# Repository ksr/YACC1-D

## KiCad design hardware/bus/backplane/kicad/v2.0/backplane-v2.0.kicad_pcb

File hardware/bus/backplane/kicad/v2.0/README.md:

# backplane-v2.0 — KiCad conversion

Generated 2026-09-23 by `tools/eagle_to_kicad_all.py` from the Eagle design `yacc2buss` in `hardware/bus/backplane/eagle/v2.0/`. **The Eagle files are the record of what was designed and built; this KiCad project is derived from them and is regenerated from scratch on every run of the tool** (hand edits here will be lost - once a card is edited in KiCad, remove it from the tool's list). This revision was FABRICATED (see `hardware/FABRICATED.md`).

## Files

| File | What it is |
|---|---|
| `backplane-v2.0.kicad_pro` | project; OSH Park rules (6 mil track, 5 mil clearance, 10 mil drill, 4 mil annular) |
| `backplane-v2.0.kicad_sch` | root sheet; 1 sub-sheet(s) `backplane-v2.0-sheetN.kicad_sch` mirror the Eagle sheets |
| `backplane-v2.0-eagle.kicad_sym` | project symbol library generated from the Eagle libraries used (units = Eagle gates) |
| `backplane-v2.0.kicad_pcb` | the board: 4 copper layers, 29 footprints, 8523 track segments, 1388 vias |
| `backplane-v2.0-eagle.pretty/` | project footprint library extracted from the imported board |
| `reports/` | ERC (`erc.json`), DRC (`drc.json`), schematic PDF, board renders (`-top.png`, `-bottom.png`), netlist + `netlist-compare.txt` |

## Proof

Schematic-vs-board netlist comparison (`tools/kicad/compare_netlists.py`: every (reference, pad) partition must be identical): **MATCH (87/87 nets)**

```
  same connectivity, different net name: [('/Sheet 1/SIG0', 'SIG0'), ('/Sheet 1/SIG1', 'SIG1'), ('/Sheet 1/SIG2', 'SIG2'), ('/Sheet 1/SIG3', 'SIG3'), ('/Sheet 1/SIG4', 'SIG4'), ('/Sheet 1/SIG5', 'SIG5'), ('/Sheet 1/SIG6', 'SIG6'), ('/Sheet 1/SIG7', 'SIG7'), ('/Sheet 1/SIG8', 'SIG8'), ('/Sheet 1/SIG9', 'SIG9'), ('/Sheet 1/SIG10', 'SIG10'), ('/Sheet 1/SIG11', 'SIG11'), ('/Sheet 1/SIG12', 'SIG12'), ('/Sheet 1/SIG13', 'SIG13'), ('/Sheet 1/SIG14', 'SIG14'), ('/Sheet 1/SIG15', 'SIG15'), ('/Sheet 1/SIG16', 'SIG16'), ('/Sheet 1/SIG17', 'SIG17'), ('/Sheet 1/SIG18', 'SIG18'), ('/Sheet 1/SIG19', 'SIG19'), ('/Sheet 1/SIG20', 'SIG20'), ('/Sheet 1/SIG21', 'SIG21'), ('/Sheet 1/SIG22', 'SIG22'), ('/Sheet 1/SIG23', 'SIG23'), ('/Sheet 1/SIG24', 'SIG24'), ('/Sheet 1/SIG25', 'SIG25'), ('/Sheet 1/SIG26', 'SIG26'), ('/Sheet 1/SIG27', 'SIG27'), ('/Sheet 1/SIG28', 'SIG28'), ('/Sheet 1/SIG29', 'SIG29'), ('/Sheet 1/SIG30', 'SIG30'), ('/Sheet 1/SIG31', 'SIG31'), ('/Sheet 1/SIG32', 'SIG32'), ('/Sheet 1/SIG33', 'SIG33'), ('/Sheet 1/SIG34', 'SIG34'), ('/Sheet 1/SIG35', 'SIG35'), ('/Sheet 1/SIG36', 'SIG36'), ('/Sheet 1/SIG37', 'SIG37'), ('/Sheet 1/SIG38', 'SIG38'), ('/Sheet 1/SIG39', 'SIG39'), ('/Sheet 1/SIG40', 'SIG40'), ('/Sheet 1/SIG41', 'SIG41'), ('/Sheet 1/SIG42', 'SIG42'), ('/Sheet 1/SIG43', 'SIG43'), ('/Sheet 1/SIG44', 'SIG44'), ('/Sheet 1/SIG45', 'SIG45'), ('/Sheet 1/SIG46', 'SIG46'), ('/Sheet 1/SIG47', 'SIG47'), ('/Sheet 1/SIG48', 'SIG48'), ('/Sheet 1/SIG49', 'SIG49'), ('/Sheet 1/SIG50', 'SIG50'), ('/Sheet 1/SIG51', 'SIG51'), ('/Sheet 1/SIG52', 'SIG52'), ('/Sheet 1/SIG53', 'SIG53'), ('/Sheet 1/SIG54', 'SIG54'), ('/Sheet 1/SIG55', 'SIG55'), ('/Sheet 1/SIG56', 'SIG56'), ('/Sheet 1/SIG57', 'SIG57'), ('/Sheet 1/SIG58', 'SIG58'), ('/Sheet 1/SIG59', 'SIG59'), ('/Sheet 1/SIG60', 'SIG60'), ('/Sheet 1/SIG61', 'SIG61'), ('/Sheet 1/SIG62', 'SIG62'), ('/Sheet 1/SIG63', 'SIG63'), ('/Sheet 1/SIG64', 'SIG64'), ('/Sheet 1/SIG65', 'SIG65'), ('/Sheet 1/SIG66', 'SIG66'), ('/Sheet 1/SIG67', 'SIG67'), ('/Sheet 1/SIG68', 'SIG68'), ('/Sheet 1/SIG69', 'SIG69'), ('/Sheet 1/SIG70', 'SIG70'), ('/Sheet 1/SIG71', 'SIG71'), ('/Sheet 1/SIG72', 'SIG72'), ('/Sheet 1/SIG73', 'SIG73'), ('/Sheet 1/SIG74', 'SIG74'), ('/Sheet 1/SIG75', 'SIG75'), ('/Sheet 1/SIG76', 'SIG76'), ('/Sheet 1/SIG77', 'SIG77'), ('/Sheet 1/SIG78', 'SIG78'), ('/Sheet 1/SIG79', 'SIG79'), ('/Sheet 1/SIG80', 'SIG80'), ('/Sheet 1/SIG81', 'SIG81'), ('/Sheet 1/SIG82', 'SIG82'), ('/Sheet 1/SIG83', 'SIG83'), ('Net-(PWR0-PadA)', 'N$2')]
```

## Readability

`tools/kicad/sch_overlaps.py` over every sheet: text over text 7, text over a symbol body 559, text crossed by a line 9, items off the drawing frame or on the title block 0. What is left is mostly the Eagle drawing itself (parts placed that close in Eagle) or KiCad drawing pin numbers centred on short pins.

## Residual ERC / DRC

ERC by type: none.
`isolated_pin_label` = the converter's per-net global labels (cosmetic); `power_pin_not_driven` / unused-unit notes are the same ones KiCad's own Eagle importer leaves. `unconnected_wire_endpoint` / `pin_not_connected` = wire stubs Eagle leaves bare (mostly net wires ending on a bus, which is drawn as graphics here); since 2026-09-23 the converter no longer hangs a label on every such end (that was most of the label clutter), so they show as KiCad warnings.

DRC by type: clearance 3, items_not_allowed 16, lib_footprint_mismatch 8, shorting_items 16, silk_over_copper 4, silk_overlap 76; unconnected items 0; schematic parity 0.
Silk-over-pad and clearance notes reflect the Eagle design as drawn; unconnected items are Eagle airwires (parts the design left unrouted).

Converter: converted: 56 symbols, 891 wires, 672 labels, 135 junctions, 8 bus lines, 0 no-connects

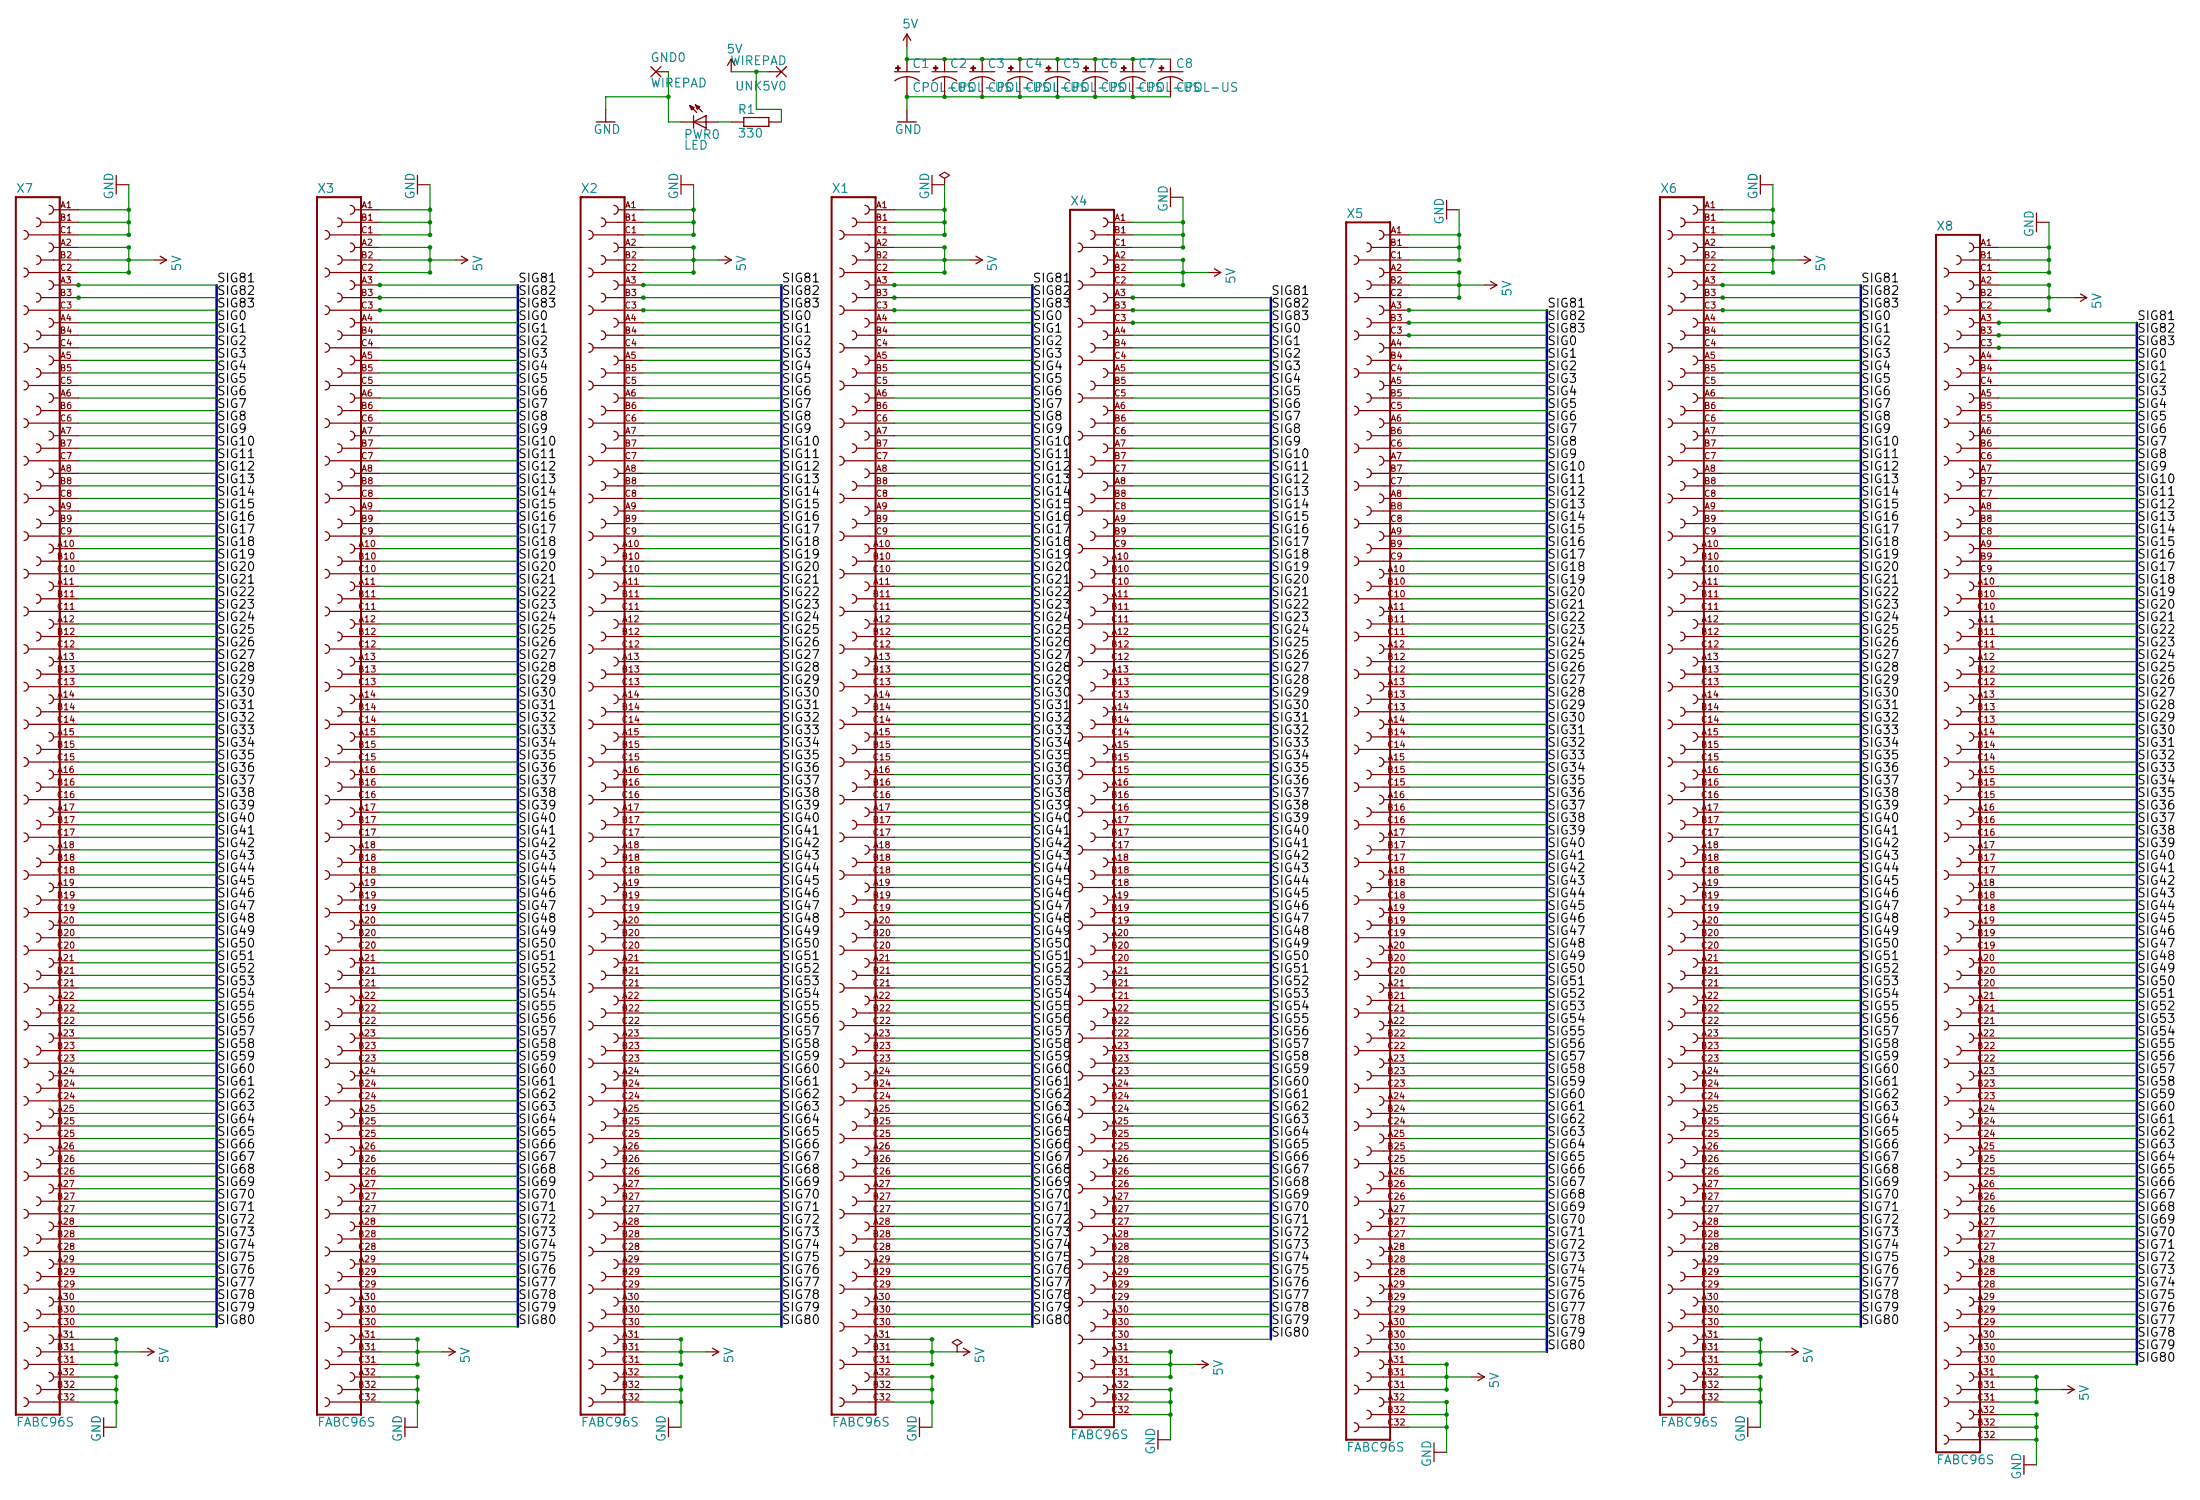
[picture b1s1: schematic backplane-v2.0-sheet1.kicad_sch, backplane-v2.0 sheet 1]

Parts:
C1, C2, C3, C4, C5, C6, C7, C8: CPOL-US; E5-6
GND0: WIREPAD; 4,16O1,6
PWR0: LED; LED5MM
R1: 330; 0207_10
UNK5V0: WIREPAD; 4,16O1,6
X1, X2, X3, X4, X5, X6, X7, X8: FABC96S

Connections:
5V: C1.+, C2.+, C3.+, C4.+, C5.+, C6.+, C7.+, C8.+, R1.2, UNK5V0.1, X1.A2, X1.A31, X1.B2, X1.B31, X1.C2, X1.C31, X2.A2, X2.A31, X2.B2, X2.B31, X2.C2, X2.C31, X3.A2, X3.A31, X3.B2, X3.B31, X3.C2, X3.C31, X4.A2, X4.A31, X4.B2, X4.B31, X4.C2, X4.C31, X5.A2, X5.A31, X5.B2, X5.B31, X5.C2, X5.C31, X6.A2, X6.A31, X6.B2, X6.B31, X6.C2, X6.C31, X7.A2, X7.A31, X7.B2, X7.B31, X7.C2, X7.C31, X8.A2, X8.A31, X8.B2, X8.B31, X8.C2, X8.C31
GND: C1.-, C2.-, C3.-, C4.-, C5.-, C6.-, C7.-, C8.-, GND0.1, PWR0.K (C), X1.A1, X1.A32, X1.B1, X1.B32, X1.C1, X1.C32, X2.A1, X2.A32, X2.B1, X2.B32, X2.C1, X2.C32, X3.A1, X3.A32, X3.B1, X3.B32, X3.C1, X3.C32, X4.A1, X4.A32, X4.B1, X4.B32, X4.C1, X4.C32, X5.A1, X5.A32, X5.B1, X5.B32, X5.C1, X5.C32, X6.A1, X6.A32, X6.B1, X6.B32, X6.C1, X6.C32, X7.A1, X7.A32, X7.B1, X7.B32, X7.C1, X7.C32, X8.A1, X8.A32, X8.B1, X8.B32, X8.C1, X8.C32
unnamed: PWR0.A, R1.1
SIG0: X1.A4, X2.A4, X3.A4, X4.A4, X5.A4, X6.A4, X7.A4, X8.A4
SIG1: X1.B4, X2.B4, X3.B4, X4.B4, X5.B4, X6.B4, X7.B4, X8.B4
SIG2: X1.C4, X2.C4, X3.C4, X4.C4, X5.C4, X6.C4, X7.C4, X8.C4
SIG3: X1.A5, X2.A5, X3.A5, X4.A5, X5.A5, X6.A5, X7.A5, X8.A5
SIG4: X1.B5, X2.B5, X3.B5, X4.B5, X5.B5, X6.B5, X7.B5, X8.B5
SIG5: X1.C5, X2.C5, X3.C5, X4.C5, X5.C5, X6.C5, X7.C5, X8.C5
SIG6: X1.A6, X2.A6, X3.A6, X4.A6, X5.A6, X6.A6, X7.A6, X8.A6
SIG7: X1.B6, X2.B6, X3.B6, X4.B6, X5.B6, X6.B6, X7.B6, X8.B6
SIG8: X1.C6, X2.C6, X3.C6, X4.C6, X5.C6, X6.C6, X7.C6, X8.C6
SIG9: X1.A7, X2.A7, X3.A7, X4.A7, X5.A7, X6.A7, X7.A7, X8.A7
SIG10: X1.B7, X2.B7, X3.B7, X4.B7, X5.B7, X6.B7, X7.B7, X8.B7
SIG11: X1.C7, X2.C7, X3.C7, X4.C7, X5.C7, X6.C7, X7.C7, X8.C7
SIG12: X1.A8, X2.A8, X3.A8, X4.A8, X5.A8, X6.A8, X7.A8, X8.A8
SIG13: X1.B8, X2.B8, X3.B8, X4.B8, X5.B8, X6.B8, X7.B8, X8.B8
SIG14: X1.C8, X2.C8, X3.C8, X4.C8, X5.C8, X6.C8, X7.C8, X8.C8
SIG15: X1.A9, X2.A9, X3.A9, X4.A9, X5.A9, X6.A9, X7.A9, X8.A9
SIG16: X1.B9, X2.B9, X3.B9, X4.B9, X5.B9, X6.B9, X7.B9, X8.B9
SIG17: X1.C9, X2.C9, X3.C9, X4.C9, X5.C9, X6.C9, X7.C9, X8.C9
SIG18: X1.A10, X2.A10, X3.A10, X4.A10, X5.A10, X6.A10, X7.A10, X8.A10
SIG19: X1.B10, X2.B10, X3.B10, X4.B10, X5.B10, X6.B10, X7.B10, X8.B10
SIG20: X1.C10, X2.C10, X3.C10, X4.C10, X5.C10, X6.C10, X7.C10, X8.C10
SIG21: X1.A11, X2.A11, X3.A11, X4.A11, X5.A11, X6.A11, X7.A11, X8.A11
SIG22: X1.B11, X2.B11, X3.B11, X4.B11, X5.B11, X6.B11, X7.B11, X8.B11
SIG23: X1.C11, X2.C11, X3.C11, X4.C11, X5.C11, X6.C11, X7.C11, X8.C11
SIG24: X1.A12, X2.A12, X3.A12, X4.A12, X5.A12, X6.A12, X7.A12, X8.A12
SIG25: X1.B12, X2.B12, X3.B12, X4.B12, X5.B12, X6.B12, X7.B12, X8.B12
SIG26: X1.C12, X2.C12, X3.C12, X4.C12, X5.C12, X6.C12, X7.C12, X8.C12
SIG27: X1.A13, X2.A13, X3.A13, X4.A13, X5.A13, X6.A13, X7.A13, X8.A13
SIG28: X1.B13, X2.B13, X3.B13, X4.B13, X5.B13, X6.B13, X7.B13, X8.B13
SIG29: X1.C13, X2.C13, X3.C13, X4.C13, X5.C13, X6.C13, X7.C13, X8.C13
SIG30: X1.A14, X2.A14, X3.A14, X4.A14, X5.A14, X6.A14, X7.A14, X8.A14
SIG31: X1.B14, X2.B14, X3.B14, X4.B14, X5.B14, X6.B14, X7.B14, X8.B14
SIG32: X1.C14, X2.C14, X3.C14, X4.C14, X5.C14, X6.C14, X7.C14, X8.C14
SIG33: X1.A15, X2.A15, X3.A15, X4.A15, X5.A15, X6.A15, X7.A15, X8.A15
SIG34: X1.B15, X2.B15, X3.B15, X4.B15, X5.B15, X6.B15, X7.B15, X8.B15
SIG35: X1.C15, X2.C15, X3.C15, X4.C15, X5.C15, X6.C15, X7.C15, X8.C15
SIG36: X1.A16, X2.A16, X3.A16, X4.A16, X5.A16, X6.A16, X7.A16, X8.A16
SIG37: X1.B16, X2.B16, X3.B16, X4.B16, X5.B16, X6.B16, X7.B16, X8.B16
SIG38: X1.C16, X2.C16, X3.C16, X4.C16, X5.C16, X6.C16, X7.C16, X8.C16
SIG39: X1.A17, X2.A17, X3.A17, X4.A17, X5.A17, X6.A17, X7.A17, X8.A17
SIG40: X1.B17, X2.B17, X3.B17, X4.B17, X5.B17, X6.B17, X7.B17, X8.B17
SIG41: X1.C17, X2.C17, X3.C17, X4.C17, X5.C17, X6.C17, X7.C17, X8.C17
SIG42: X1.A18, X2.A18, X3.A18, X4.A18, X5.A18, X6.A18, X7.A18, X8.A18
SIG43: X1.B18, X2.B18, X3.B18, X4.B18, X5.B18, X6.B18, X7.B18, X8.B18
SIG44: X1.C18, X2.C18, X3.C18, X4.C18, X5.C18, X6.C18, X7.C18, X8.C18
SIG45: X1.A19, X2.A19, X3.A19, X4.A19, X5.A19, X6.A19, X7.A19, X8.A19
SIG46: X1.B19, X2.B19, X3.B19, X4.B19, X5.B19, X6.B19, X7.B19, X8.B19
SIG47: X1.C19, X2.C19, X3.C19, X4.C19, X5.C19, X6.C19, X7.C19, X8.C19
SIG48: X1.A20, X2.A20, X3.A20, X4.A20, X5.A20, X6.A20, X7.A20, X8.A20
SIG49: X1.B20, X2.B20, X3.B20, X4.B20, X5.B20, X6.B20, X7.B20, X8.B20
SIG50: X1.C20, X2.C20, X3.C20, X4.C20, X5.C20, X6.C20, X7.C20, X8.C20
SIG51: X1.A21, X2.A21, X3.A21, X4.A21, X5.A21, X6.A21, X7.A21, X8.A21
SIG52: X1.B21, X2.B21, X3.B21, X4.B21, X5.B21, X6.B21, X7.B21, X8.B21
SIG53: X1.C21, X2.C21, X3.C21, X4.C21, X5.C21, X6.C21, X7.C21, X8.C21
SIG54: X1.A22, X2.A22, X3.A22, X4.A22, X5.A22, X6.A22, X7.A22, X8.A22
SIG55: X1.B22, X2.B22, X3.B22, X4.B22, X5.B22, X6.B22, X7.B22, X8.B22
SIG56: X1.C22, X2.C22, X3.C22, X4.C22, X5.C22, X6.C22, X7.C22, X8.C22
SIG57: X1.A23, X2.A23, X3.A23, X4.A23, X5.A23, X6.A23, X7.A23, X8.A23
SIG58: X1.B23, X2.B23, X3.B23, X4.B23, X5.B23, X6.B23, X7.B23, X8.B23
SIG59: X1.C23, X2.C23, X3.C23, X4.C23, X5.C23, X6.C23, X7.C23, X8.C23
SIG60: X1.A24, X2.A24, X3.A24, X4.A24, X5.A24, X6.A24, X7.A24, X8.A24
SIG61: X1.B24, X2.B24, X3.B24, X4.B24, X5.B24, X6.B24, X7.B24, X8.B24
SIG62: X1.C24, X2.C24, X3.C24, X4.C24, X5.C24, X6.C24, X7.C24, X8.C24
SIG63: X1.A25, X2.A25, X3.A25, X4.A25, X5.A25, X6.A25, X7.A25, X8.A25
SIG64: X1.B25, X2.B25, X3.B25, X4.B25, X5.B25, X6.B25, X7.B25, X8.B25
SIG65: X1.C25, X2.C25, X3.C25, X4.C25, X5.C25, X6.C25, X7.C25, X8.C25
SIG66: X1.A26, X2.A26, X3.A26, X4.A26, X5.A26, X6.A26, X7.A26, X8.A26
SIG67: X1.B26, X2.B26, X3.B26, X4.B26, X5.B26, X6.B26, X7.B26, X8.B26
SIG68: X1.C26, X2.C26, X3.C26, X4.C26, X5.C26, X6.C26, X7.C26, X8.C26
SIG69: X1.A27, X2.A27, X3.A27, X4.A27, X5.A27, X6.A27, X7.A27, X8.A27
SIG70: X1.B27, X2.B27, X3.B27, X4.B27, X5.B27, X6.B27, X7.B27, X8.B27
SIG71: X1.C27, X2.C27, X3.C27, X4.C27, X5.C27, X6.C27, X7.C27, X8.C27
SIG72: X1.A28, X2.A28, X3.A28, X4.A28, X5.A28, X6.A28, X7.A28, X8.A28
SIG73: X1.B28, X2.B28, X3.B28, X4.B28, X5.B28, X6.B28, X7.B28, X8.B28
SIG74: X1.C28, X2.C28, X3.C28, X4.C28, X5.C28, X6.C28, X7.C28, X8.C28
SIG75: X1.A29, X2.A29, X3.A29, X4.A29, X5.A29, X6.A29, X7.A29, X8.A29
SIG76: X1.B29, X2.B29, X3.B29, X4.B29, X5.B29, X6.B29, X7.B29, X8.B29
SIG77: X1.C29, X2.C29, X3.C29, X4.C29, X5.C29, X6.C29, X7.C29, X8.C29
SIG78: X1.A30, X2.A30, X3.A30, X4.A30, X5.A30, X6.A30, X7.A30, X8.A30
SIG79: X1.B30, X2.B30, X3.B30, X4.B30, X5.B30, X6.B30, X7.B30, X8.B30
SIG80: X1.C30, X2.C30, X3.C30, X4.C30, X5.C30, X6.C30, X7.C30, X8.C30
SIG81: X1.A3, X2.A3, X3.A3, X4.A3, X5.A3, X6.A3, X7.A3, X8.A3
SIG82: X1.B3, X2.B3, X3.B3, X4.B3, X5.B3, X6.B3, X7.B3, X8.B3
SIG83: X1.C3, X2.C3, X3.C3, X4.C3, X5.C3, X6.C3, X7.C3, X8.C3

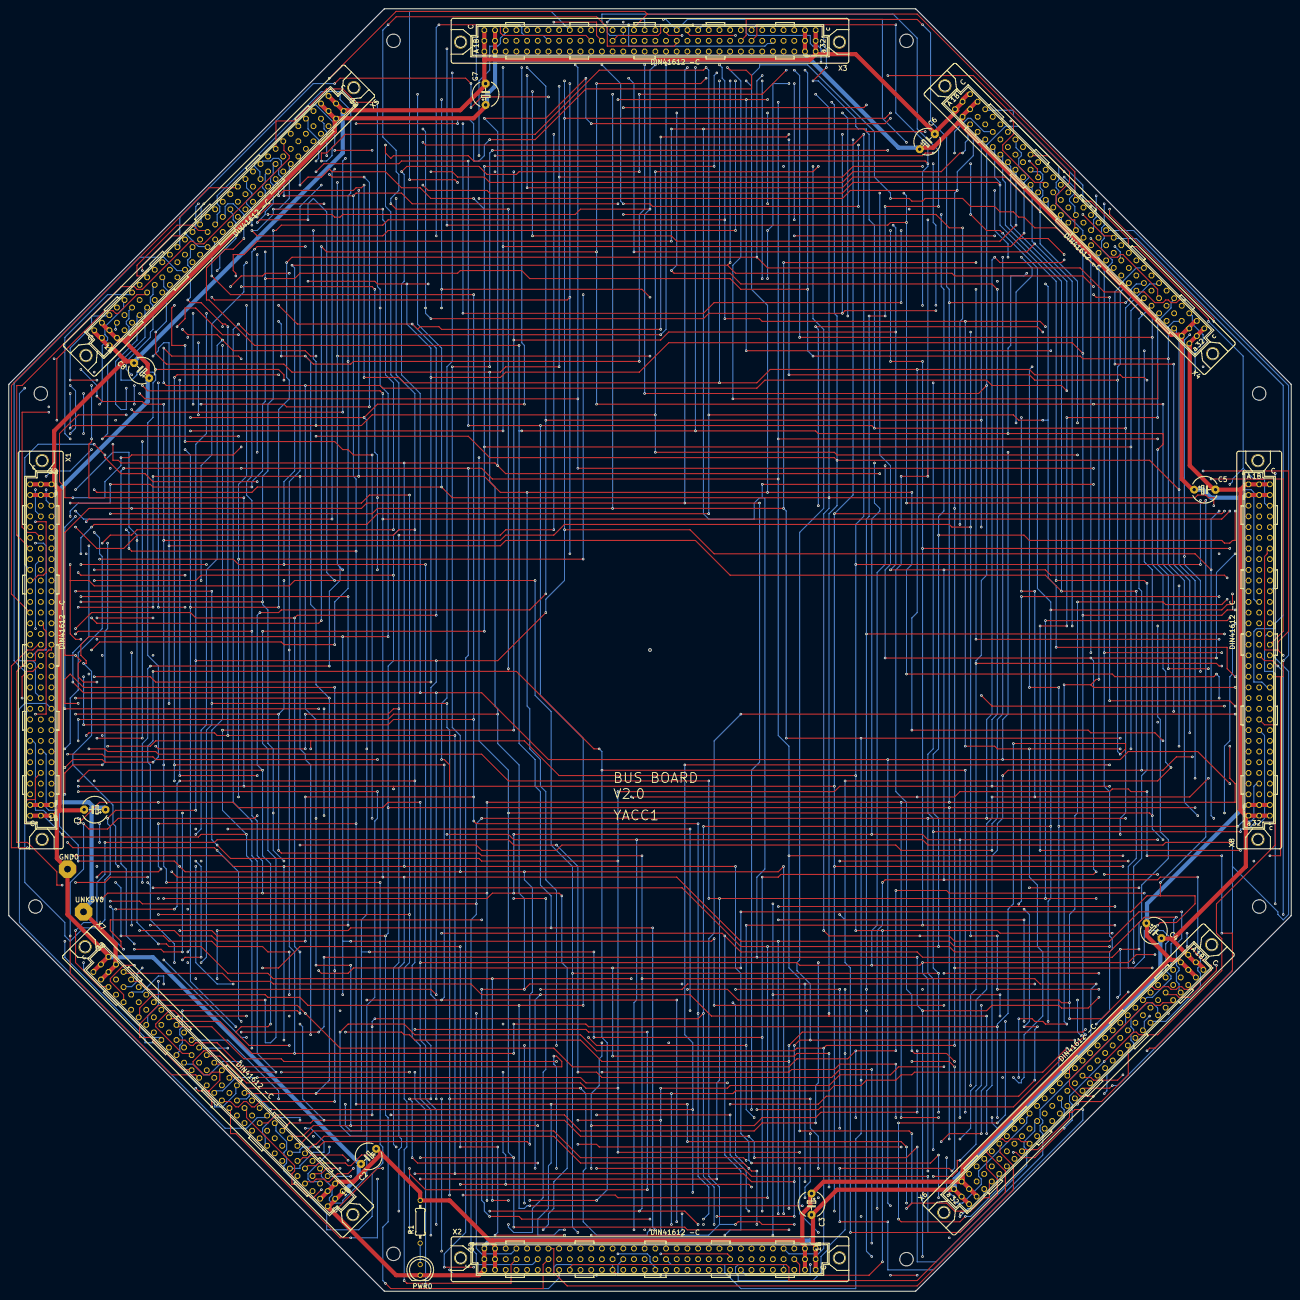
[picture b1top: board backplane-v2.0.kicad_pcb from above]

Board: 4 copper layers, 304.8 x 304.8 mm, 29 parts (0 on the bottom side), 87 nets.

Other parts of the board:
UNK_HOLE_0: dummyfp0
UNK_HOLE_1: dummyfp1
UNK_HOLE_2: dummyfp2
UNK_HOLE_3: dummyfp3
UNK_HOLE_4: dummyfp4
UNK_HOLE_5: dummyfp5
UNK_HOLE_6: dummyfp6
UNK_HOLE_7: dummyfp7
UNK_HOLE_8: dummyfp8

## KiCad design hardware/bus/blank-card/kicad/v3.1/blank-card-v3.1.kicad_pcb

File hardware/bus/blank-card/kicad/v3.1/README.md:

# blank-card-v3.1 — KiCad conversion

Generated 2026-09-23 by `tools/eagle_to_kicad_all.py` from the Eagle design `Blank V3.1` in `hardware/bus/blank-card/eagle/v3.1/`. **The Eagle files are the record of what was designed and built; this KiCad project is derived from them and is regenerated from scratch on every run of the tool** (hand edits here will be lost - once a card is edited in KiCad, remove it from the tool's list). This revision was FABRICATED (see `hardware/FABRICATED.md`).

## Files

| File | What it is |
|---|---|
| `blank-card-v3.1.kicad_pro` | project; OSH Park rules (6 mil track, 5 mil clearance, 10 mil drill, 4 mil annular) |
| `blank-card-v3.1.kicad_sch` | root sheet; 1 sub-sheet(s) `blank-card-v3.1-sheetN.kicad_sch` mirror the Eagle sheets |
| `blank-card-v3.1-eagle.kicad_sym` | project symbol library generated from the Eagle libraries used (units = Eagle gates) |
| `blank-card-v3.1.kicad_pcb` | the board: 2 copper layers, 3 footprints, 21 track segments, 0 vias |
| `blank-card-v3.1-eagle.pretty/` | project footprint library extracted from the imported board |
| `reports/` | ERC (`erc.json`), DRC (`drc.json`), schematic PDF, board renders (`-top.png`, `-bottom.png`), netlist + `netlist-compare.txt` |

## Proof

Schematic-vs-board netlist comparison (`tools/kicad/compare_netlists.py`: every (reference, pad) partition must be identical): **MATCH (3/3 nets)**

```
  same connectivity, different net name: [('Net-(PWR0-PadA)', 'N$11')]
```

## Readability

`tools/kicad/sch_overlaps.py` over every sheet: text over text 0, text over a symbol body 0, text crossed by a line 0, items off the drawing frame or on the title block 0. What is left is mostly the Eagle drawing itself (parts placed that close in Eagle) or KiCad drawing pin numbers centred on short pins.

## Residual ERC / DRC

ERC by type: isolated_pin_label 84.
`isolated_pin_label` = the converter's per-net global labels (cosmetic); `power_pin_not_driven` / unused-unit notes are the same ones KiCad's own Eagle importer leaves. `unconnected_wire_endpoint` / `pin_not_connected` = wire stubs Eagle leaves bare (mostly net wires ending on a bus, which is drawn as graphics here); since 2026-09-23 the converter no longer hangs a label on every such end (that was most of the label clutter), so they show as KiCad warnings.

DRC by type: items_not_allowed 2, lib_footprint_mismatch 1, silk_edge_clearance 4, text_height 2; unconnected items 0; schematic parity 0.
Silk-over-pad and clearance notes reflect the Eagle design as drawn; unconnected items are Eagle airwires (parts the design left unrouted).

Converter: converted: 100 symbols, 113 wires, 84 labels, 11 junctions, 1 bus lines, 0 no-connects

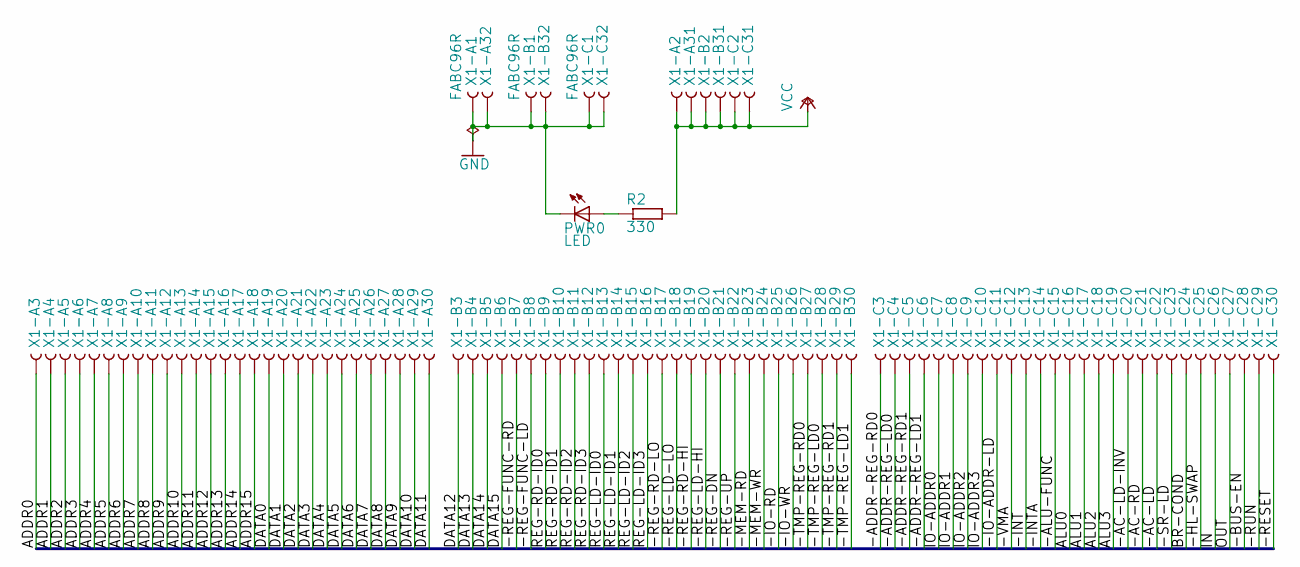
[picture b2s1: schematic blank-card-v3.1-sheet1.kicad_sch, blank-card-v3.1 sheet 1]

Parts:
PWR0: LED; LED5MM
R2: 330; 0207_10
X1: FABC96R

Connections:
-AC-LD: X1.C22
-AC-LD-INV: X1.C20
-AC-RD: X1.C21
-ADDR-REG-LD0: X1.C4
-ADDR-REG-LD1: X1.C6
-ADDR-REG-RD0: X1.C3
-ADDR-REG-RD1: X1.C5
-ALU-FUNC: X1.C15
-BUS-EN: X1.C28
-HL-SWAP: X1.C25
-INT: X1.C13
-INTA: X1.C14
-IO-ADDR-LD: X1.C11
-IO-RD: X1.B25
-IO-WR: X1.B26
-MEM-RD: X1.B23
-MEM-WR: X1.B24
-REG-DN: X1.B21
-REG-FUNC-LD: X1.B8
-REG-FUNC-RD: X1.B7
-REG-LD-HI: X1.B20
-REG-LD-LO: X1.B18
-REG-RD-HI: X1.B19
-REG-RD-LO: X1.B17
-REG-UP: X1.B22
-RESET: X1.C30
-RUN: X1.C29
-SR-LD: X1.C23
-TMP-REG-LD0: X1.B28
-TMP-REG-LD1: X1.B30
-TMP-REG-RD0: X1.B27
-TMP-REG-RD1: X1.B29
-VMA: X1.C12
ADDR0: X1.A3
ADDR1: X1.A4
ADDR2: X1.A5
ADDR3: X1.A6
ADDR4: X1.A7
ADDR5: X1.A8
ADDR6: X1.A9
ADDR7: X1.A10
ADDR8: X1.A11
ADDR9: X1.A12
ADDR10: X1.A13
ADDR11: X1.A14
ADDR12: X1.A15
ADDR13: X1.A16
ADDR14: X1.A17
ADDR15: X1.A18
ALU0: X1.C16
ALU1: X1.C17
ALU2: X1.C18
ALU3: X1.C19
BR-COND: X1.C24
DATA0: X1.A19
DATA1: X1.A20
DATA2: X1.A21
DATA3: X1.A22
DATA4: X1.A23
DATA5: X1.A24
DATA6: X1.A25
DATA7: X1.A26
DATA8: X1.A27
DATA9: X1.A28
DATA10: X1.A29
DATA11: X1.A30
DATA12: X1.B3
DATA13: X1.B4
DATA14: X1.B5
DATA15: X1.B6
GND: PWR0.K (C), X1.A1, X1.A32, X1.B1, X1.B32, X1.C1, X1.C32
IN: X1.C26
IO-ADDR0: X1.C7
IO-ADDR1: X1.C8
IO-ADDR2: X1.C9
IO-ADDR3: X1.C10
unnamed: PWR0.A, R2.1
OUT: X1.C27
REG-LD-ID0: X1.B13
REG-LD-ID1: X1.B14
REG-LD-ID2: X1.B15
REG-LD-ID3: X1.B16
REG-RD-ID0: X1.B9
REG-RD-ID1: X1.B10
REG-RD-ID2: X1.B11
REG-RD-ID3: X1.B12
VCC: R2.2, X1.A2, X1.A31, X1.B2, X1.B31, X1.C2, X1.C31

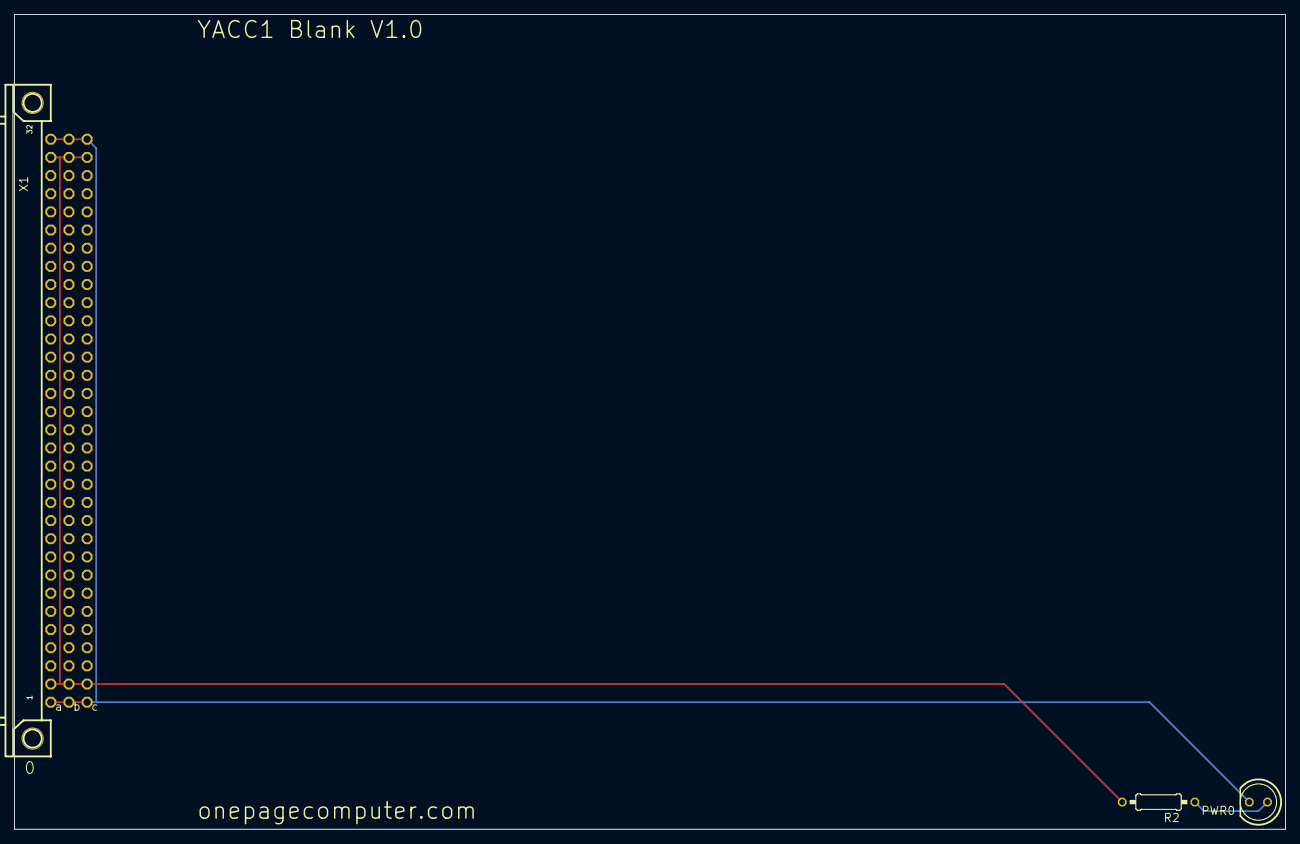
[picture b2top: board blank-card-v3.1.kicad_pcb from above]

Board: 2 copper layers, 177.8 x 114.0 mm, 3 parts (0 on the bottom side), 3 nets.

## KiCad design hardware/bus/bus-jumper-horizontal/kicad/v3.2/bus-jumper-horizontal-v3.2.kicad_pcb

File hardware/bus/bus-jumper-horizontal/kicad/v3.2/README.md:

# bus-jumper-horizontal-v3.2 — KiCad conversion

Generated 2026-09-23 by `tools/eagle_to_kicad_all.py` from the Eagle design `Jumper Board Horizontal V3.1` in `hardware/bus/bus-jumper-horizontal/eagle/v3.2/`. **The Eagle files are the record of what was designed and built; this KiCad project is derived from them and is regenerated from scratch on every run of the tool** (hand edits here will be lost - once a card is edited in KiCad, remove it from the tool's list). This revision was FABRICATED (see `hardware/FABRICATED.md`).

## Files

| File | What it is |
|---|---|
| `bus-jumper-horizontal-v3.2.kicad_pro` | project; OSH Park rules (6 mil track, 5 mil clearance, 10 mil drill, 4 mil annular) |
| `bus-jumper-horizontal-v3.2.kicad_sch` | root sheet; 1 sub-sheet(s) `bus-jumper-horizontal-v3.2-sheetN.kicad_sch` mirror the Eagle sheets |
| `bus-jumper-horizontal-v3.2-eagle.kicad_sym` | project symbol library generated from the Eagle libraries used (units = Eagle gates) |
| `bus-jumper-horizontal-v3.2.kicad_pcb` | the board: 4 copper layers, 7 footprints, 1130 track segments, 229 vias |
| `bus-jumper-horizontal-v3.2-eagle.pretty/` | project footprint library extracted from the imported board |
| `reports/` | ERC (`erc.json`), DRC (`drc.json`), schematic PDF, board renders (`-top.png`, `-bottom.png`), netlist + `netlist-compare.txt` |

## Proof

Schematic-vs-board netlist comparison (`tools/kicad/compare_netlists.py`: every (reference, pad) partition must be identical): **MATCH (89/89 nets)**

```
  same connectivity, different net name: [('/Sheet 1/GND', 'GND'), ('/Sheet 1/V1', 'V1'), ('/Sheet 1/V2', 'V2'), ('Net-(PWR1-PadA)', 'N$35'), ('Net-(PWR2-PadA)', 'N$36'), ('Net-(X3AA-S)', 'N$29'), ('Net-(X3AB-S)', 'N$30'), ('Net-(X3AC-S)', 'N$31'), ('Net-(X3AD-S)', 'N$32'), ('Net-(X3AI-S)', 'N$37'), ('Net-(X3AJ-S)', 'N$38'), ('Net-(X3AK-S)', 'N$39'), ('Net-(X3AL-S)', 'N$40'), ('Net-(X3AM-S)', 'N$41'), ('Net-(X3AN-S)', 'N$42'), ('Net-(X3AO-S)', 'N$43'), ('Net-(X3AP-S)', 'N$44'), ('Net-(X3AQ-S)', 'N$45'), ('Net-(X3AR-S)', 'N$46'), ('Net-(X3AS-S)', 'N$47'), ('Net-(X3AT-S)', 'N$48'), ('Net-(X3AU-S)', 'N$49'), ('Net-(X3AV-S)', 'N$50'), ('Net-(X3AW-S)', 'N$51'), ('Net-(X3AX-S)', 'N$52'), ('Net-(X3AY-S)', 'N$53'), ('Net-(X3AZ-S)', 'N$54'), ('Net-(X3BA-S)', 'N$55'), ('Net-(X3BB-S)', 'N$56'), ('Net-(X3BC-S)', 'N$57'), ('Net-(X3BD-S)', 'N$58'), ('Net-(X3BE-S)', 'N$59'), ('Net-(X3BF-S)', 'N$60'), ('Net-(X3BG-S)', 'N$61'), ('Net-(X3BH-S)', 'N$62'), ('Net-(X3BI-S)', 'N$63'), ('Net-(X3BJ-S)', 'N$64'), ('Net-(X3BO-S)', 'N$69'), ('Net-(X3BP-S)', 'N$70'), ('Net-(X3BQ-S)', 'N$71'), ('Net-(X3BR-S)', 'N$72'), ('Net-(X3BS-S)', 'N$73'), ('Net-(X3BT-S)', 'N$74'), ('Net-(X3BU-S)', 'N$75'), ('Net-(X3BV-S)', 'N$76'), ('Net-(X3BW-S)', 'N$77'), ('Net-(X3BX-S)', 'N$78'), ('Net-(X3BY-S)', 'N$79'), ('Net-(X3BZ-S)', 'N$80'), ('Net-(X3C-S)', 'N$4'), ('Net-(X3CA-S)', 'N$81'), ('Net-(X3CB-S)', 'N$82'), ('Net-(X3CC-S)', 'N$83'), ('Net-(X3CD-S)', 'N$84'), ('Net-(X3CE-S)', 'N$85'), ('Net-(X3CF-S)', 'N$86'), ('Net-(X3CG-S)', 'N$87'), ('Net-(X3CH-S)', 'N$88'), ('Net-(X3CI-S)', 'N$89'), ('Net-(X3CJ-S)', 'N$90'), ('Net-(X3CK-S)', 'N$91'), ('Net-(X3CL-S)', 'N$92'), ('Net-(X3CM-S)', 'N$93'), ('Net-(X3CN-S)', 'N$94'), ('Net-(X3CO-S)', 'N$95'), ('Net-(X3CP-S)', 'N$96'), ('Net-(X3D-S)', 'N$6'), ('Net-(X3E-S)', 'N$7'), ('Net-(X3F-S)', 'N$8'), ('Net-(X3G-S)', 'N$9'), ('Net-(X3H-S)', 'N$10'), ('Net-(X3I-S)', 'N$11'), ('Net-(X3J-S)', 'N$12'), ('Net-(X3K-S)', 'N$13'), ('Net-(X3L-S)', 'N$14'), ('Net-(X3M-S)', 'N$15'), ('Net-(X3N-S)', 'N$16'), ('Net-(X3O-S)', 'N$17'), ('Net-(X3P-S)', 'N$18'), ('Net-(X3Q-S)', 'N$19'), ('Net-(X3R-S)', 'N$20'), ('Net-(X3S-S)', 'N$21'), ('Net-(X3T-S)', 'N$22'), ('Net-(X3U-S)', 'N$23'), ('Net-(X3V-S)', 'N$24'), ('Net-(X3W-S)', 'N$25'), ('Net-(X3X-S)', 'N$26'), ('Net-(X3Y-S)', 'N$27'), ('Net-(X3Z-S)', 'N$28')]
```

## Readability

`tools/kicad/sch_overlaps.py` over every sheet: text over text 0, text over a symbol body 0, text crossed by a line 0, items off the drawing frame or on the title block 0. What is left is mostly the Eagle drawing itself (parts placed that close in Eagle) or KiCad drawing pin numbers centred on short pins.

## Residual ERC / DRC

ERC by type: none.
`isolated_pin_label` = the converter's per-net global labels (cosmetic); `power_pin_not_driven` / unused-unit notes are the same ones KiCad's own Eagle importer leaves. `unconnected_wire_endpoint` / `pin_not_connected` = wire stubs Eagle leaves bare (mostly net wires ending on a bus, which is drawn as graphics here); since 2026-09-23 the converter no longer hangs a label on every such end (that was most of the label clutter), so they show as KiCad warnings.

DRC by type: isolated_copper 1, items_not_allowed 4, lib_footprint_mismatch 2, silk_over_copper 6, silk_overlap 16; unconnected items 1; schematic parity 0.
Silk-over-pad and clearance notes reflect the Eagle design as drawn; unconnected items are Eagle airwires (parts the design left unrouted).

Converter: converted: 197 symbols, 112 wires, 22 labels, 0 junctions, 0 bus lines, 0 no-connects

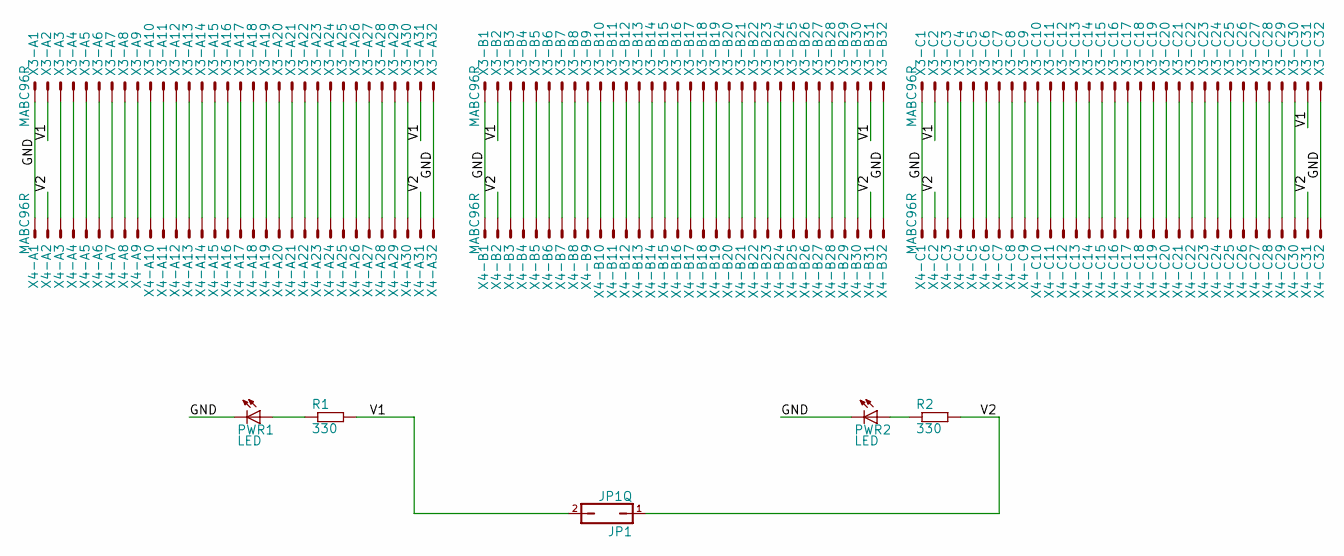
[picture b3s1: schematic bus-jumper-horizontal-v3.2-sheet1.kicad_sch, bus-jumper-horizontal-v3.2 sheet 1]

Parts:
JP1: JP1Q; JP1
PWR1, PWR2: LED; LED5MM
R1, R2: 330; 0207_10
X3, X4: MABC96R

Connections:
GND: PWR1.K (C), PWR2.K (C), X3.A1, X3.A32, X3.B1, X3.B32, X3.C1, X3.C32, X4.A1, X4.A32, X4.B1, X4.B32, X4.C1, X4.C32
unnamed: X3.A3, X4.A3
unnamed: X3.A4, X4.A4
unnamed: X3.A5, X4.A5
unnamed: X3.A6, X4.A6
unnamed: X3.A7, X4.A7
unnamed: X3.A8, X4.A8
unnamed: X3.A9, X4.A9
unnamed: X3.A10, X4.A10
unnamed: X3.A11, X4.A11
unnamed: X3.A12, X4.A12
unnamed: X3.A13, X4.A13
unnamed: X3.A14, X4.A14
unnamed: X3.A15, X4.A15
unnamed: X3.A16, X4.A16
unnamed: X3.A17, X4.A17
unnamed: X3.A18, X4.A18
unnamed: X3.A19, X4.A19
unnamed: X3.A20, X4.A20
unnamed: X3.A21, X4.A21
unnamed: X3.A22, X4.A22
unnamed: X3.A23, X4.A23
unnamed: X3.A24, X4.A24
unnamed: X3.A25, X4.A25
unnamed: X3.A26, X4.A26
unnamed: X3.A27, X4.A27
unnamed: X3.A28, X4.A28
unnamed: X3.A29, X4.A29
unnamed: X3.A30, X4.A30
unnamed: PWR1.A, R1.1
unnamed: PWR2.A, R2.1
unnamed: X3.B3, X4.B3
unnamed: X3.B4, X4.B4
unnamed: X3.B5, X4.B5
unnamed: X3.B6, X4.B6
unnamed: X3.B7, X4.B7
unnamed: X3.B8, X4.B8
unnamed: X3.B9, X4.B9
unnamed: X3.B10, X4.B10
unnamed: X3.B11, X4.B11
unnamed: X3.B12, X4.B12
unnamed: X3.B13, X4.B13
unnamed: X3.B14, X4.B14
unnamed: X3.B15, X4.B15
unnamed: X3.B16, X4.B16
unnamed: X3.B17, X4.B17
unnamed: X3.B18, X4.B18
unnamed: X3.B19, X4.B19
unnamed: X3.B20, X4.B20
unnamed: X3.B21, X4.B21
unnamed: X3.B22, X4.B22
unnamed: X3.B23, X4.B23
unnamed: X3.B24, X4.B24
unnamed: X3.B25, X4.B25
unnamed: X3.B26, X4.B26
unnamed: X3.B27, X4.B27
unnamed: X3.B28, X4.B28
unnamed: X3.B29, X4.B29
unnamed: X3.B30, X4.B30
unnamed: X3.C3, X4.C3
unnamed: X3.C4, X4.C4
unnamed: X3.C5, X4.C5
unnamed: X3.C6, X4.C6
unnamed: X3.C7, X4.C7
unnamed: X3.C8, X4.C8
unnamed: X3.C9, X4.C9
unnamed: X3.C10, X4.C10
unnamed: X3.C11, X4.C11
unnamed: X3.C12, X4.C12
unnamed: X3.C13, X4.C13
unnamed: X3.C14, X4.C14
unnamed: X3.C15, X4.C15
unnamed: X3.C16, X4.C16
unnamed: X3.C17, X4.C17
unnamed: X3.C18, X4.C18
unnamed: X3.C19, X4.C19
unnamed: X3.C20, X4.C20
unnamed: X3.C21, X4.C21
unnamed: X3.C22, X4.C22
unnamed: X3.C23, X4.C23
unnamed: X3.C24, X4.C24
unnamed: X3.C25, X4.C25
unnamed: X3.C26, X4.C26
unnamed: X3.C27, X4.C27
unnamed: X3.C28, X4.C28
unnamed: X3.C29, X4.C29
unnamed: X3.C30, X4.C30
V1: JP1.2, R1.2, X3.A2, X3.A31, X3.B2, X3.B31, X3.C2, X3.C31
V2: JP1.1, R2.2, X4.A2, X4.A31, X4.B2, X4.B31, X4.C2, X4.C31

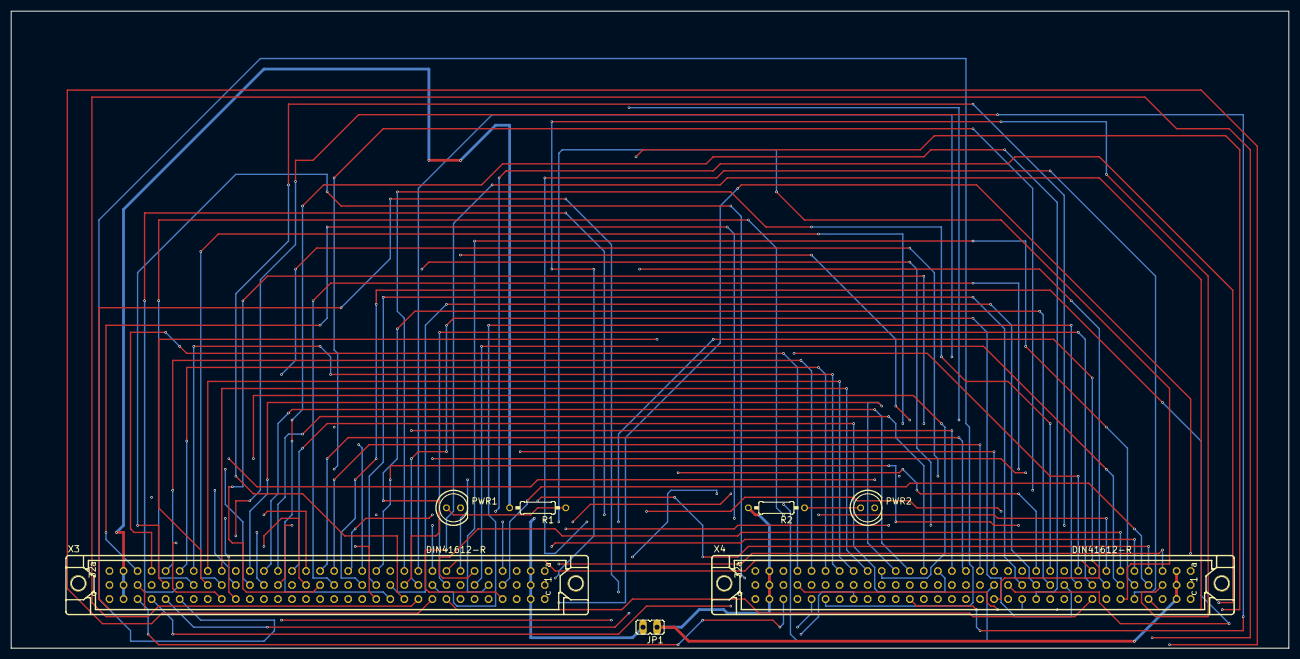
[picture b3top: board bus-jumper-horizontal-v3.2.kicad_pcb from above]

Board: 4 copper layers, 231.1 x 115.2 mm, 7 parts (0 on the bottom side), 89 nets.
